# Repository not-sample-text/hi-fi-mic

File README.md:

# Hi-Fi Microphone PCB

A custom PCB for the high-fidelity microphone project by DIY Perks, redesigned from the original stripboard version for a cleaner and more reliable build.

## Table of Contents

- [Overview](#overview)
- [Features](#features)
- [PCB Design](#pcb-design)
- [Project Structure](#project-structure)
- [Getting Started](#getting-started)
- [Credits](#credits)

## Overview

This project provides a dedicated PCB for the Hi-Fi microphone circuit originally demonstrated by [DIY Perks](https://www.youtube.com/watch?v=LoQu3XXIayc). While the original build used a stripboard, this KiCad project offers a custom-designed PCB, making the assembly process more straightforward and the final product more durable and professional.

## Features

- **Dedicated PCB Design**: Eliminates complex wiring on stripboard, improving reliability.
- **Compact & Clean Layout**: Components are organized for a tidy and space-efficient build.
- **Easy Assembly**: Through-hole components and clear labeling simplify the soldering process.
- **Professional Finish**: Achieve a high-quality result comparable to commercial products.

## PCB Design

The project was designed in KiCad and consists of a single two-layer board.

- **[Schematic PDF](<mic_base/Other Files/mic_base_schematic.pdf>)**
- **[PCB Layout PDF](<mic_base/Other Files/mic_base_layout.pdf>)**

### PCB Renders

|                       Front View                      |                        Back View                          |                         Initial Design                        |
| :---------------------------------------------------: | :-------------------------------------------------------: | :-----------------------------------------------------------: |
|  |  |  |

## Project Structure

```
hi-fi-mic/
├── Imports/                  # Custom 3D models, footprints, and symbols
├── Other Files/              # Documentation (PDFs) and images
├── mic_base.kicad_pcb        # KiCad PCB layout file
├── mic_base.kicad_pro        # Main KiCad project file
├── mic_base.kicad_sch        # KiCad schematic file
└── README.md                 # This file
```

## Getting Started

### Hardware Assembly

1.  **Manufacture the PCB**: Use the KiCad project files to export Gerbers and order the board from a PCB fabrication service.
2.  **Gather Components**: Refer to the schematic for the complete Bill of Materials (BOM).
3.  **Solder Components**: Assemble the board, starting with the lowest-profile components first.
4.  **Testing**: Follow the testing and calibration steps shown in the original [DIY Perks video](https://www.youtube.com/watch?v=LoQu3XXIayc).

### Opening the Project

1.  Install [KiCad](https://www.kicad.org/) 7.0 or later.
2.  Open the `mic_base.kicad_pro` file to access the schematic and PCB layout.

## Credits

- **Original Circuit Concept**: [DIY Perks](https://www.youtube.com/c/DIYPerks)
- **PCB Redesign**: This project.

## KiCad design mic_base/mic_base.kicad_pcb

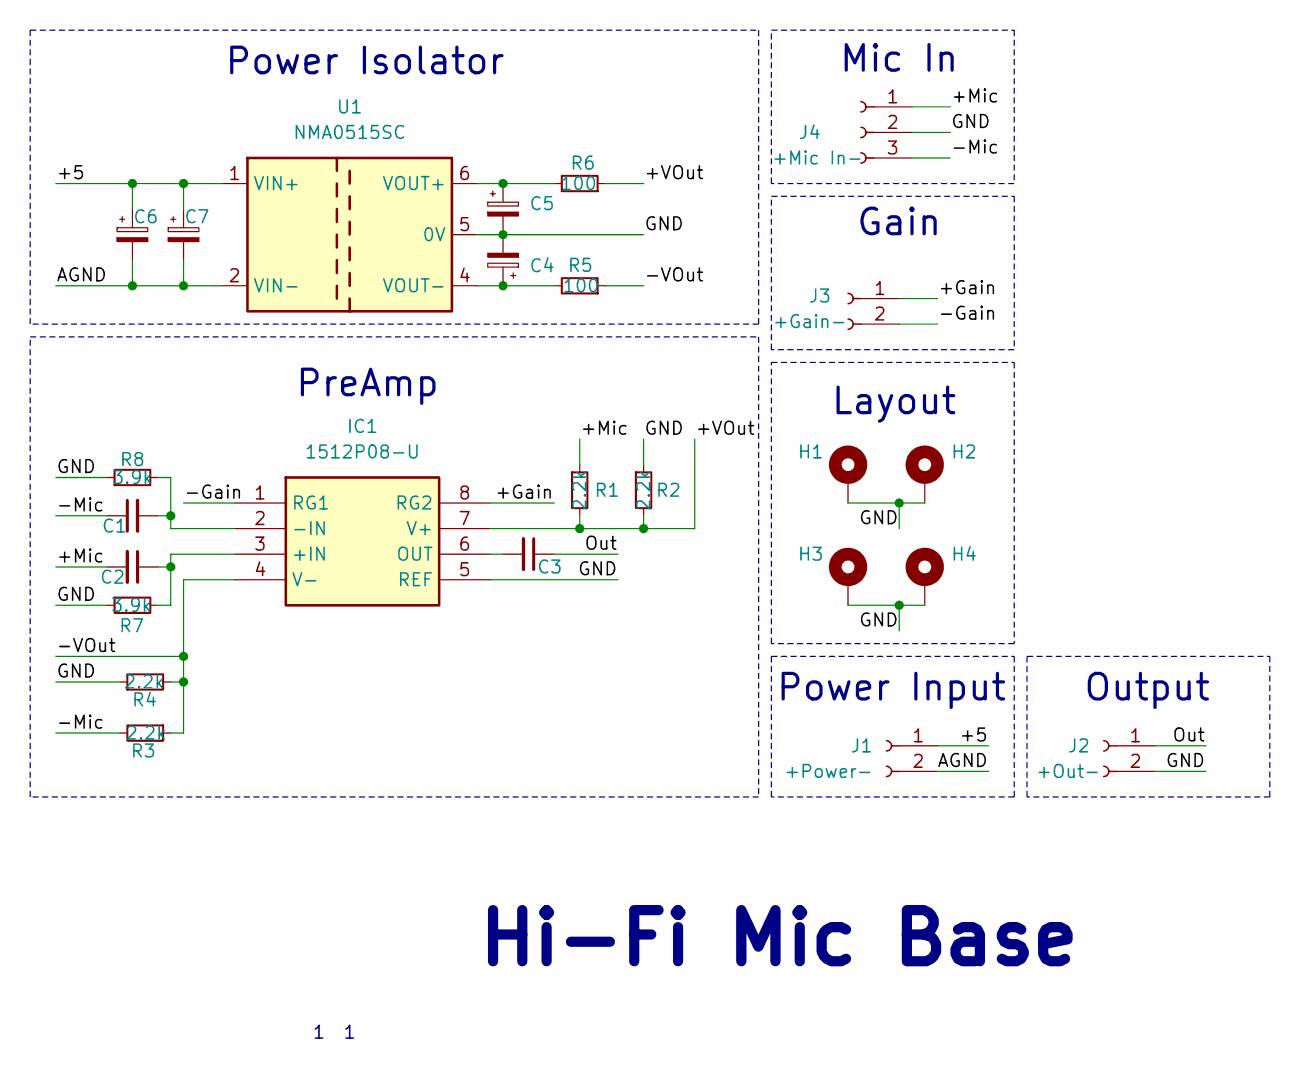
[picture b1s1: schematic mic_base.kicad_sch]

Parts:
C1, C2, C3: 22uF; C_0805_2012Metric
C4, C5, C6, C7: 2200uF; CP_Radial_D10.0mm_P5.00mm
H1, H2, H3, H4: MountingHole_Pad; MountingHole_2.2mm_M2_DIN965_Pad
IC1: 1512P08-U; DIP781W46P254L952H432Q8N; Mouser Part Number 887-1512P08-U
J1: +Power-; JST_XH_B2B-XH-A_1x02_P2.50mm_Vertical
J2: +Out-; JST_XH_B2B-XH-A_1x02_P2.50mm_Vertical
J3: +Gain-; JST_XH_B2B-XH-A_1x02_P2.50mm_Vertical
J4: +Mic In-; JST_XH_B3B-XH-A_1x03_P2.50mm_Vertical
R1, R2, R3, R4: 2.2k; R_0805_2012Metric
R5, R6: 100; R_0805_2012Metric
R7, R8: 3.9k; R_0805_2012Metric
U1: NMA0515SC; Converter_DCDC_Murata_NMAxxxxSC_THT

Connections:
/+5: C6.1, C7.1, J1.1, U1.1 (VIN+)
/+Gain: IC1.8 (RG2), J3.1
/+Mic: C2.2, J4.1, R1.1
/+VOut: IC1.7 (V+), R1.2, R2.2, R6.1
/-Gain: IC1.1 (RG1), J3.2
/-Mic: C1.1, J4.3, R3.2
/-VOut: IC1.4 (V-), R3.1, R4.2, R5.1
/AGND: C6.2, C7.2, J1.2, U1.2 (VIN-)
/GND: C4.2, C5.2, H1.1, H2.1, H3.1, H4.1, IC1.5 (REF), J2.2, J4.2, R2.1, R4.1, R7.1, R8.1, U1.5 (0V)
/Out: C3.1, J2.1
unnamed: C2.1, IC1.3 (+IN), R7.2
unnamed: C1.2, IC1.2 (-IN), R8.2
unnamed: C3.2, IC1.6 (OUT)
unnamed: C5.1, R6.2, U1.6 (VOUT+)
unnamed: C4.1, R5.2, U1.4 (VOUT-)

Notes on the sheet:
Output
Gain
PreAmp
Power Isolator
Mic In
Layout
Power Input
Hi-Fi Mic Base

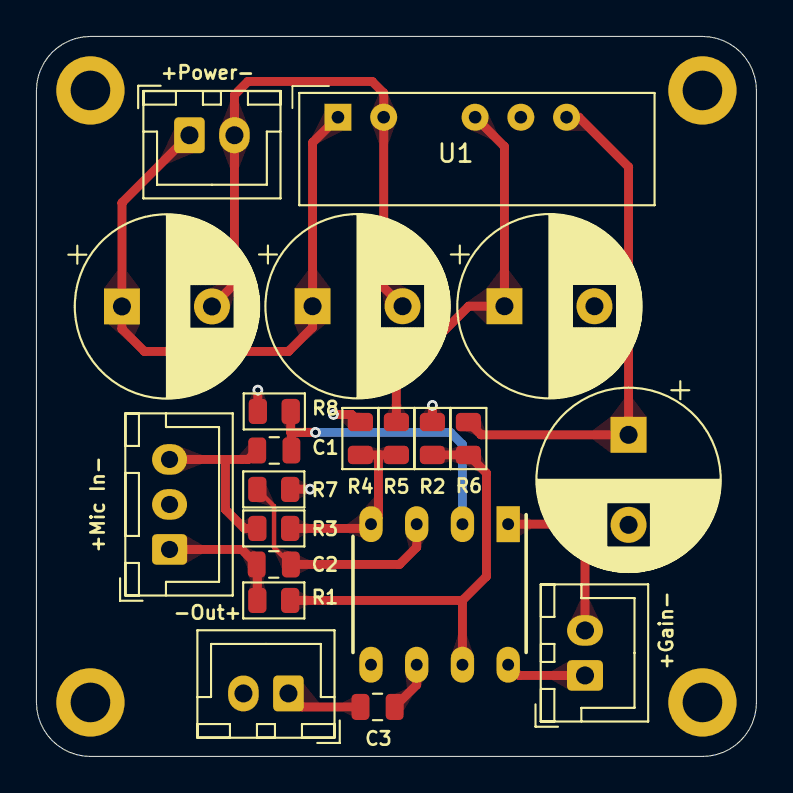
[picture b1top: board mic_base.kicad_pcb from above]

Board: 2 copper layers, 40.0 x 40.0 mm, 25 parts (0 on the bottom side), 15 nets.

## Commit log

2025-10-14 basically done, maybe add some finishing touches later
2025-10-24 moved capacitors, made pcb smaller
2025-10-24 added images and readme
2025-10-26 changed resistors pin pitch from 7 to 5, compressed the board more
    readme to be updated
2025-10-27 changed footprints to 0805 smds, rewrote the readme
2025-10-27 repaired readme
